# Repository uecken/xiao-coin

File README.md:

"# xiao-coin"
準備中...
Preparing now...

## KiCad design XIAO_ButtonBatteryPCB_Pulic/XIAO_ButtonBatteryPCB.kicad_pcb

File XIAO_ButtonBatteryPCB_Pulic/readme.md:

電源スイッチの代替は下記などをご利用ください。

 - 小型スライドスイッチ 1回路2接点 SS12D01G4
https://akizukidenshi.com/catalog/g/g112723/

- スライドスイッチ 1回路2接点 基板用 横向き
https://akizukidenshi.com/catalog/g/g115704/

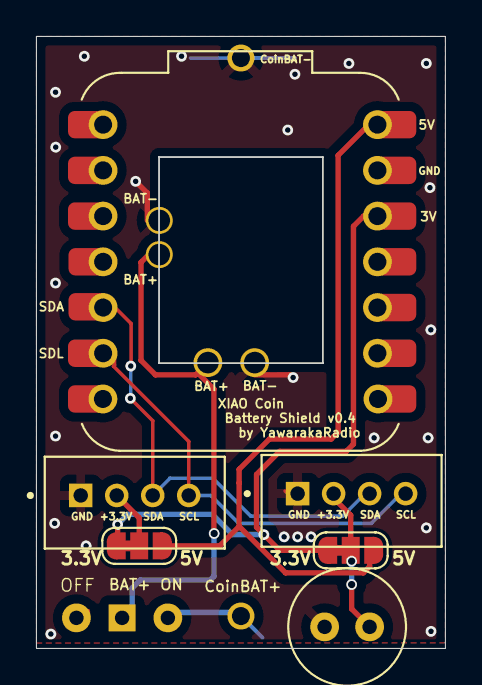
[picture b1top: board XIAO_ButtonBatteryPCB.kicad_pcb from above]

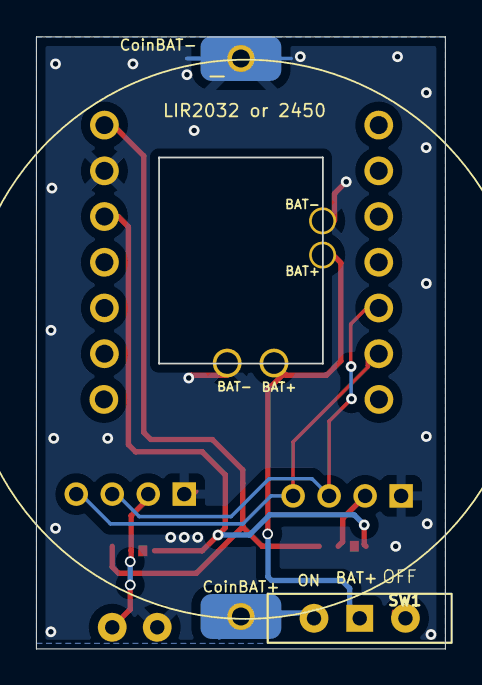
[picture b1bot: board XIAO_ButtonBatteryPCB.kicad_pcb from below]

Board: 2 copper layers, 22.7 x 34.0 mm, 8 parts (2 on the bottom side), 8 nets.

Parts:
C1: C; C_Radial_D6.3mm_H7.0mm_P2.50mm
C4: C; 2450_MYOUNG BS-24-B4AK014
J1, J2: 110990030__Grove; SEEED_110990030
JP1, JP2: SolderJumper_3_Bridged12; SolderJumper-3_P1.3mm_Bridged12_RoundedPad1.0x1.5mm_NumberL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
SW1: MK-12D13G4-B; SW_Slide-03_Wuerth-WS-SLTV_10x2.5x6.4_P2.54mm
U1: XIAO-ESP32C3_C6; XIAO_Seeed_ESP32C3_C6_BatteryHolder_v2.1

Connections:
/+3.3V: JP1.1 (A), JP2.1 (A), U1.12 (3V3)
/+5V: JP1.3 (B), JP2.3 (B), U1.14 (5V)
/Grove1_Vcc: C1.2, J1.2 (Vcc), JP1.2 (C)
/Grove2_Vcc: J2.2 (Vcc), JP2.2 (C)
/SCL: J1.4 (SCL), J2.4 (SCL), U1.6 (PA9_A5_D5_SCL)
/SDA: J1.3 (SDA), J2.3 (SDA), U1.5 (PA8_A4_D4_SDA)
GND: C1.1, C4.2, J1.1 (GND), J2.1 (GND), U1.13 (GND), U1.16 (Vbat-), U1.27 (Vbat-)
unnamed: SW1.1 (B), U1.17 (Vbat+), U1.26 (Vbat+)

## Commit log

2024-12-10 preparing
2025-05-27 add micropython
2025-05-27 canged tp simple BON085
2025-05-27 add XIAO PCB
2025-05-27 まだできない
2025-05-28 v1.0
2025-05-28 add readme
2025-05-28 add 代替電源スイッチ
2025-06-02 update pdf
2025-07-03 Castellated Holes = No
